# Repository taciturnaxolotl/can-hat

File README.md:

# CANopy

The canonical repo for this is hosted on tangled over at [`dunkirk.sh/CANopy`](https://tangled.org/dunkirk.sh/CANopy)

## BOM

| Name | Purpose | Quantity | Total Cost (USD) | Distributor |
|---|---|---|---|---|
| [2×20 40-pin stacking female header](https://www.amazon.com/dp/B0827THC7R) | 15-16mm pin length to clear Pi 5 active cooler, hand solder | 1 | $9.90 | Amazon |
| [10kΩ 0603](https://www.lcsc.com/product-detail/C25803.html) | MCP2518FD RESET pull-up and MCP2562FD STBY pull-down, PCBA | 100 | $0.18 | LCSC |
| [1kΩ 0603](https://www.lcsc.com/product-detail/C21190.html) | EEPROM write-protect pull-up to 3.3V, PCBA | 100 | $0.16 | LCSC |
| [3.9kΩ 0603](https://www.lcsc.com/product-detail/C23196.html) | EEPROM SDA/SCL pull-ups to 3.3V, PCBA | 100 | $0.16 | LCSC |
| [120Ω 0603](https://www.lcsc.com/product-detail/C25879.html) | CAN bus termination resistors, one per channel, PCBA | 100 | $0.09 | LCSC |
| [10µF 0805](https://www.lcsc.com/product-detail/C15850.html) | Bulk caps for 3.3V and 5V rails, PCBA | 20 | $0.43 | LCSC |
| [1µF 0603 X5R](https://www.lcsc.com/product-detail/C15849.html) | Decoupling caps for all ICs, PCBA | 100 | $0.56 | LCSC |
| [15EDGRC-3.5-02P (plug & header)](https://www.lcsc.com/product-detail/C5632692.html) | PCB-side right-angle pluggable terminal block, 3.5mm pitch, 2-pin, hand solder | 10 | $3.21 | LCSC |
| [AT24C32D-SSHM-T](https://www.lcsc.com/product-detail/C60583.html) | 32Kbit I2C EEPROM for HAT ID, SOIC-8, hand solder | 5 | $1.48 | LCSC |
| [OVETGLJANF-40MHZ](https://www.lcsc.com/product-detail/C295515.html) | 40MHz active oscillator, 3.3V, SMD5032-4P, hand solder | 11 | $6.14 | LCSC |
| [MCP2562FDT-E/SN](https://www.lcsc.com/product-detail/C511335.html) | CAN FD transceiver with VIO pin, SOIC-8, hand solder | 11 | $12.87 | LCSC |
| [MCP2518FDT-H/SL](https://www.lcsc.com/product-detail/C626759.html) | CAN FD SPI controller, SOIC-14, hand solder | 11 | $27.07 | LCSC |

For use with the SystemCore the RSL can be emulated via the following

```python
# pseudocode
gpio = /sys/class/gpio/gpioXX/value
while True:
  enabled = read("/sys/kernel/can_heartbeat/enabledro")
  gpio.write(enabled)
  # add blink pattern logic for disabled state
  sleep(0.05)
```

### todo

- [ ] add testpoints on i2c and can rx/tx 0.1" header
- [ ] add termination resister jumper (dip switch block)
- [ ] add rsl mosfet switching ground
- [ ] [5v 5a pololu](https://www.pololu.com/product/2851)
- [ ] new screw blocks [DEGSON DG500-5.08-02P-14-00A(H)](https://www.lcsc.com/product-detail/C691859.html)
- [ ] esd diodes on the gpio pins for rsl
- [ ] 120 ohm differential pairs for can

<p align="center">
    <i><code>&copy; 2026-present <a href="https://dunkirk.sh">Kieran Klukas</a></code></i>
</p>

<p align="center">
    
</p>

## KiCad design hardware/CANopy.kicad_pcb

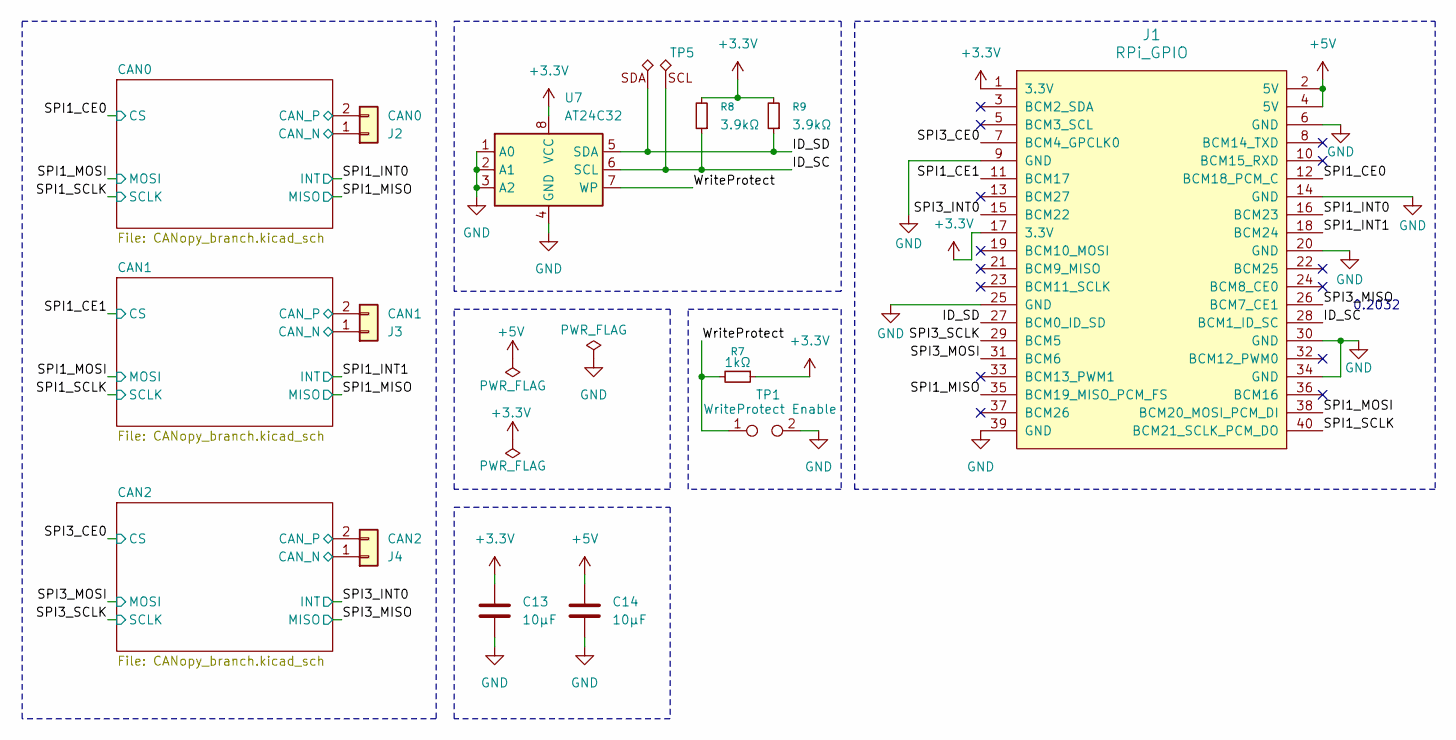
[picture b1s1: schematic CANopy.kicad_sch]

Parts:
C13, C14: 10µF; C_0805_2012Metric; LCSC C15850
J1: RPi_GPIO; RPI_Hat_B+
J2: CAN0; CONN-TH_DG500-5.08-02P-14-00A-H; LCSC C5632692
J3: CAN1; CONN-TH_DG500-5.08-02P-14-00A-H; LCSC C5632692
J4: CAN2; CONN-TH_DG500-5.08-02P-14-00A-H; LCSC C5632692
R7: 1kΩ; R_0603_1608Metric; LCSC C21190
R8, R9: 3.9kΩ; R_0603_1608Metric; LCSC C23196
TP1: WriteProtect Enable; TestPoint_2Pads_Pitch2.54mm_Drill0.8mm
TP5: SDA SCL
U7: AT24C32; SOIC-8_3.9x4.9mm_P1.27mm; LCSC C60583

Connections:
+3.3V: C13.1, J1.1 (3.3V), J1.17 (3.3V), R7.1, R8.2, R9.2, U7.8 (VCC); also elsewhere on the board
+5V: C14.1, J1.2 (5V), J1.4 (5V); also elsewhere on the board
/CAN0/CAN_N: J2.1; also elsewhere on the board
/CAN0/CAN_P: J2.2; also elsewhere on the board
/CAN1/CAN_N: J3.1; also elsewhere on the board
/CAN1/CAN_P: J3.2; also elsewhere on the board
/CAN2/CAN_N: J4.1; also elsewhere on the board
/CAN2/CAN_P: J4.2; also elsewhere on the board
/ID_SC: J1.28 (BCM1_ID_SC), R8.1, TP5.1, U7.6 (SCL)
/ID_SD: J1.27 (BCM0_ID_SD), R9.1, TP5.1, U7.5 (SDA)
/SPI1_CE0: J1.12 (BCM18_PCM_C); also elsewhere on the board
/SPI1_CE1: J1.11 (BCM17); also elsewhere on the board
/SPI1_INT0: J1.16 (BCM23); also elsewhere on the board
/SPI1_INT1: J1.18 (BCM24); also elsewhere on the board
/SPI1_MISO: J1.35 (BCM19_MISO_PCM_FS); also elsewhere on the board
/SPI1_MOSI: J1.38 (BCM20_MOSI_PCM_DI); also elsewhere on the board
/SPI1_SCLK: J1.40 (BCM21_SCLK_PCM_DO); also elsewhere on the board
/SPI3_CE0: J1.7 (BCM4_GPCLK0); also elsewhere on the board
/SPI3_INT0: J1.15 (BCM22); also elsewhere on the board
/SPI3_MISO: J1.26 (BCM7_CE1); also elsewhere on the board
/SPI3_MOSI: J1.31 (BCM6); also elsewhere on the board
/SPI3_SCLK: J1.29 (BCM5); also elsewhere on the board
/WriteProtect: R7.2, TP1.1, U7.7 (WP)
GND: C13.2, C14.2, J1.6 (GND), J1.9 (GND), J1.14 (GND), J1.20 (GND), J1.25 (GND), J1.30 (GND), J1.34 (GND), J1.39 (GND), TP1.2, U7.1 (A0), U7.2 (A1), U7.3 (A2), U7.4 (GND); also elsewhere on the board

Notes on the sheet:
0.2032

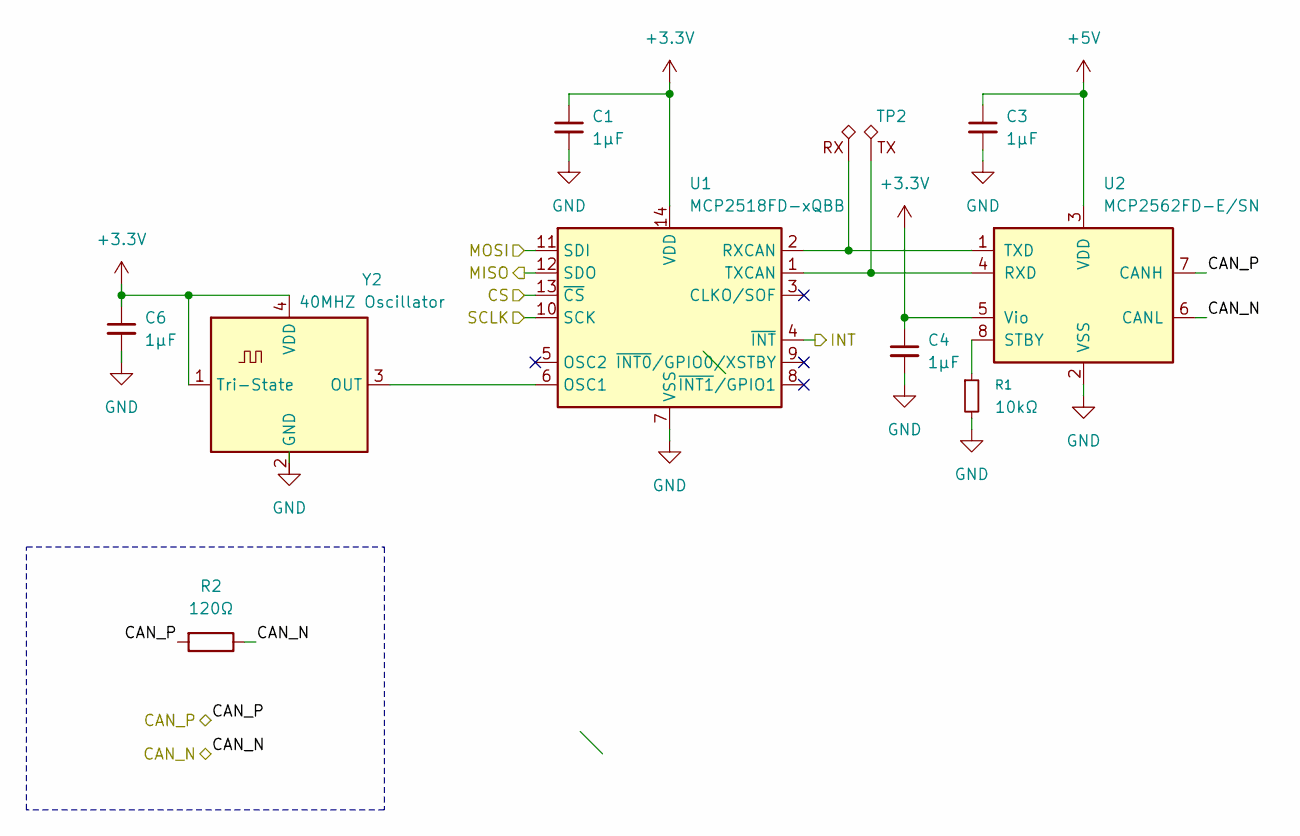
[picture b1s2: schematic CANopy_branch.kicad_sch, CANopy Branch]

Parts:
C1, C3, C4, C6: 1µF; C_0603_1608Metric; LCSC C14663
R1: 10kΩ; R_0603_1608Metric; LCSC C25803
R2: 120Ω; R_0603_1608Metric; LCSC C25879
TP2: CAN INTER RX TX
U1: MCP2518FD-xQBB; SOIC-14_L8.7-W3.9-P1.27-LS6.0-BL; LCSC C626759
U2: MCP2562FD-E/SN; SOIC-8_3.9x4.9mm_P1.27mm; LCSC C511335
Y2: 40MHZ Oscillator; Crystal_SMD_5032-4Pin_5.0x3.2mm; LCSC C295515

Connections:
+3.3V: C1.1, C4.1, C6.1, U1.14 (VDD), U2.5 (Vio), Y2.1 (Tri-State), Y2.4 (VDD); also elsewhere on the board
+5V: C3.1, U2.3 (VDD); also elsewhere on the board
/CAN0/CAN_N: R2.1, U2.6 (CANL); also elsewhere on the board
/CAN0/CAN_P: R2.2, U2.7 (CANH); also elsewhere on the board
/SPI1_CE0: U1.13 (~CS); also elsewhere on the board
/SPI1_INT0: U1.4 (~INT); also elsewhere on the board
/SPI1_MISO: U1.12 (SDO); also elsewhere on the board
/SPI1_MOSI: U1.11 (SDI); also elsewhere on the board
/SPI1_SCLK: U1.10 (SCK); also elsewhere on the board
GND: C1.2, C3.2, C4.2, C6.2, R1.2, U1.7 (VSS), U1.15 (VSS), U2.2 (VSS); also elsewhere on the board
unnamed: U1.2 (RXCAN), U2.1 (TXD)
unnamed: U1.1 (TXCAN), U2.4 (RXD)
unnamed: U1.6 (OSC1), Y2.3 (OUT)
unnamed: R1.1, U2.8 (STBY)

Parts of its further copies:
C2, C5, C7, C8, C9, C10, C11, C12: 1µF; C_0603_1608Metric; LCSC C14663
R3, R5: 120Ω; R_0603_1608Metric; LCSC C25879
R4, R6: 10kΩ; R_0603_1608Metric; LCSC C25803
U3, U5: MCP2518FD-xQBB; SOIC-14_L8.7-W3.9-P1.27-LS6.0-BL; LCSC C626759
U4, U6: MCP2562FD-E/SN; SOIC-8_3.9x4.9mm_P1.27mm; LCSC C511335
Y1, Y3: 40MHZ Oscillator; Crystal_SMD_5032-4Pin_5.0x3.2mm; LCSC C295515

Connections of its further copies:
+3.3V: C2.1, C5.1, C7.1, C9.1, C10.1, C11.1, U3.14 (VDD), U4.5 (Vio), U5.14 (VDD), U6.5 (Vio), Y1.1 (Tri-State), Y1.4 (VDD), Y3.1 (Tri-State), Y3.4 (VDD); also elsewhere on the board
+5V: C8.1, C12.1, U4.3 (VDD), U6.3 (VDD); also elsewhere on the board
/CAN1/CAN_N: R3.1, U4.6 (CANL); also elsewhere on the board
/CAN1/CAN_P: R3.2, U4.7 (CANH); also elsewhere on the board
/CAN2/CAN_N: R5.1, U6.6 (CANL); also elsewhere on the board
/CAN2/CAN_P: R5.2, U6.7 (CANH); also elsewhere on the board
/SPI1_CE1: U3.13 (~CS); also elsewhere on the board
/SPI1_INT1: U3.4 (~INT); also elsewhere on the board
/SPI1_MISO: U3.12 (SDO); also elsewhere on the board
/SPI1_MOSI: U3.11 (SDI); also elsewhere on the board
/SPI1_SCLK: U3.10 (SCK); also elsewhere on the board
/SPI3_CE0: U5.13 (~CS); also elsewhere on the board
/SPI3_INT0: U5.4 (~INT); also elsewhere on the board
/SPI3_MISO: U5.12 (SDO); also elsewhere on the board
/SPI3_MOSI: U5.11 (SDI); also elsewhere on the board
/SPI3_SCLK: U5.10 (SCK); also elsewhere on the board
GND: C2.2, C5.2, C7.2, C8.2, C9.2, C10.2, C11.2, C12.2, R4.2, R6.2, U3.7 (VSS), U4.2 (VSS), U5.7 (VSS), U6.2 (VSS); also elsewhere on the board
unnamed: U3.2 (RXCAN), U4.1 (TXD)
unnamed: U3.1 (TXCAN), U4.4 (RXD)
unnamed: U5.2 (RXCAN), U6.1 (TXD)
unnamed: U5.1 (TXCAN), U6.4 (RXD)
unnamed: U3.6 (OSC1), Y1.3 (OUT)
unnamed: R4.1, U4.8 (STBY)
unnamed: U5.6 (OSC1), Y3.3 (OUT)
unnamed: R6.1, U6.8 (STBY)

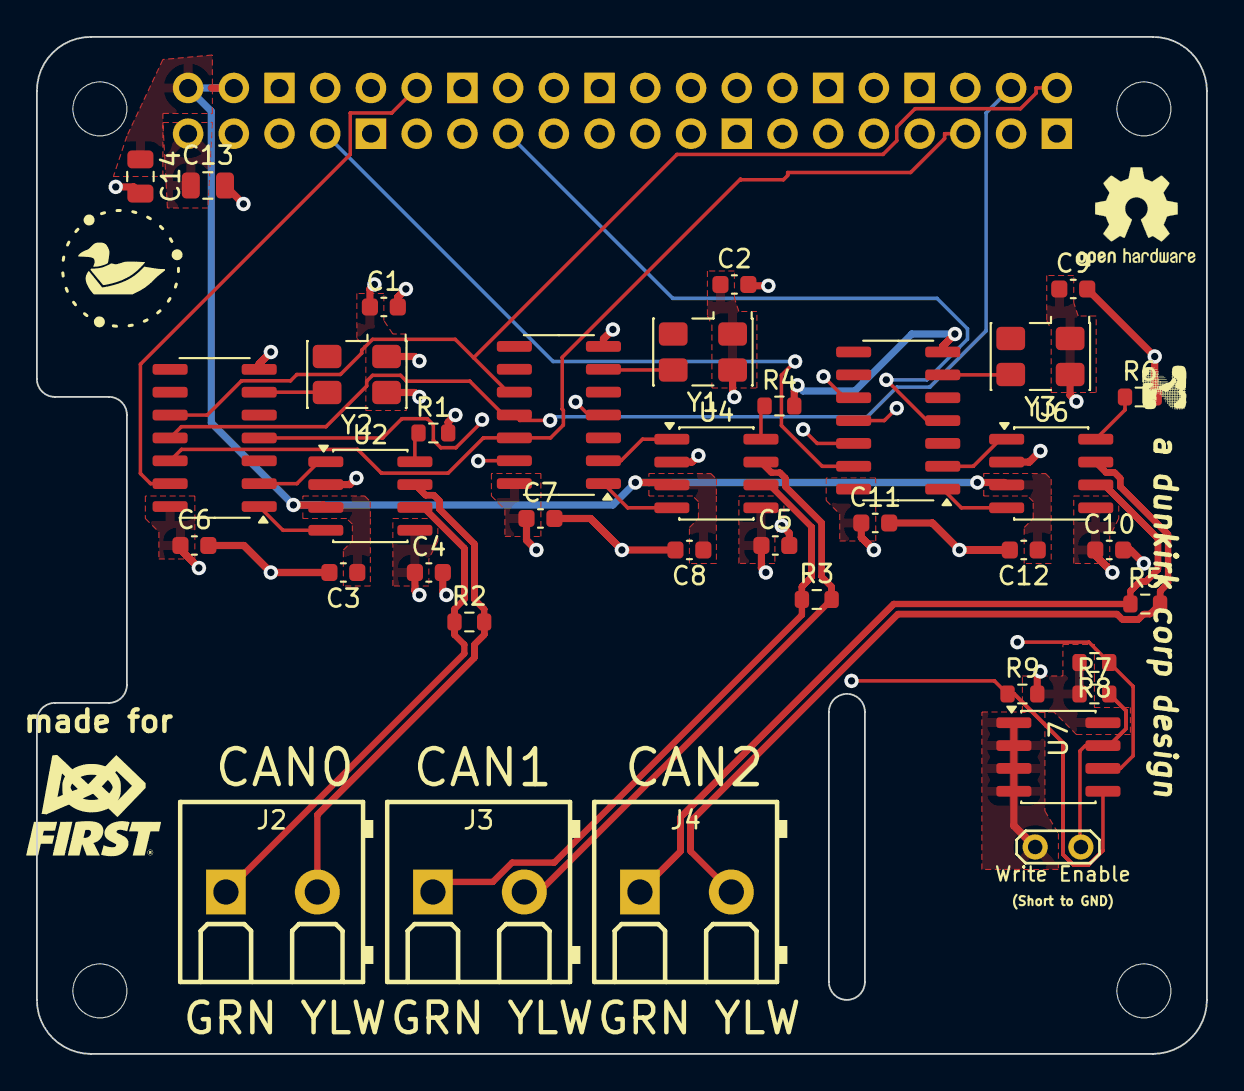
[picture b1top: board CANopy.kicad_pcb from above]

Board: 4 copper layers, 65.0 x 56.5 mm, 41 parts (0 on the bottom side), 36 nets.

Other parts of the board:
duck-logo: LOGO
first-logo: LOGO
osh-hw: OSHW-Logo2_7.3x6mm_SilkScreen

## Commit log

2026-04-25 Add project templates
2026-04-25 feat: init project
2026-04-25 feat: add can channels
2026-04-26 feat: finish the schematic
2026-04-26 docs: update readme
2026-04-26 feat: finish pcb
2026-04-26 chore: add parts and fix bom
2026-04-26 feat: rename to CANopy
2026-04-27 feat: update schematic with proper cap sizes
2026-04-28 chore: add todos
2026-05-01 feat: first pass reroute
2026-05-01 feat: route 4 layer

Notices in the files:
README.md:
https://img.shields.io/static/v1.svg?style=for-the-badge&label=License&message=CERN-OHL-S%20v2&logoColor=d9e0ee&colorA=363a4f&colorB=b7bdf8
